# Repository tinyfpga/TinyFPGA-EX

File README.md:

# TinyFPGA-EX
Small, but powerful FPGA development board based on the Lattice ECP5.

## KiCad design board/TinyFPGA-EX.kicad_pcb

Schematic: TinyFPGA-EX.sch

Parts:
C1, C17, C20, C42, C43: 1uF; C_0402_NoSilk
C2, C3, C6, C9, C10, C13, C15, C18, C24, C26, C28, C29, C30, C34, C39, C41, C44, C45, C46, C47: 100nF; C_0402_NoSilk
C4, C7, C11, C12, C14, C16, C31, C35: 10nf; C_0402_NoSilk
C5, C23: 10uF; C_0603
C8, C38, C40: 10nF; C_0402_NoSilk
C19: 2.2uF; C_0402_NoSilk
C22: 22uF; C_0603
C33: 10uF; C_0402_NoSilk
C36, C37: 1nF; C_0402_NoSilk
D1, D2: LED; LED_0603
J1: Conn_02x03_Odd_Even
J2: Micro_SD_Card_Det_Hirose_DM3AT; DM3D-SF
J3: USBC
J4, J5: Conn_01x24; Pin_Header_Straight_1x24_Pitch2.54mm
J6: Conn_02x09_Odd_Even
J7: Conn_01x06
L1: 330nH; L_Vishay_IHLP-1616
L2: 1uH; L_Wuerth_MAPI-2010
R3, R8: 0; R_0402_NoSilk
R4, R5, R7, R10: 4.7k; R_0402_NoSilk
R6: 100K; R_0402_NoSilk
R11: 1.5k; R_0402_NoSilk
R12, R13: 4.7K; R_0402_NoSilk
SW1: SW_Push; PTS_810_SMT_Switch
TP1, TP11, TP12, TP13: TEST; small-testpoint
U1: LFE5UM-285
U2: S27KS0641DPBHI020; FBGA-24
U3: DSC6001CI2A-016.0000T; CDFN3225-4LD-PL-1
U4: FAN53555; WLCSP-20
U5: MIC5504-2.5YMT-TR; Thin-DFN4
U6: Conn_02x03_Counter_Clockwise
U7: FAN53600; WLCSP-6
U8: S25FL064L; UNF008
U9: MIC5504-1.2YMT-TR; Thin-DFN4
U10, U11: PUSB3FR4Z

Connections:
+1V1: C10.1, C12.1, C13.1, C14.1, C15.1, C16.1, C22.1, L1.2, U1.C8, U1.C9, U1.C10, U1.C11, U1.D8, U1.D9, U1.D10, U1.D11, U1.J3, U1.J4, U1.J5, U1.J14, U1.J15, U1.J16, U1.K3, U1.K4, U1.K15, U1.K16, U1.L3, U1.L4, U1.L15, U1.L16, U1.M3, U1.M4, U1.M15, U1.M16, U1.P7, U1.P9, U1.P11, U4.A4; also elsewhere on the board
+1V2A: C36.1, C37.1, C38.1, C39.1, C40.1, C41.1, C43.1, TP1.1, U1.P10, U1.R10, U1.T5, U1.U6, U1.U8, U1.U12, U9.1
+2V5: C6.1, C7.1, C20.1, TP13.1, U1.E6, U1.E13, U1.N6, U1.P5, U1.P13, U1.R3, U5.1
+5V: C5.1, C8.1, C19.1, J3.A4, J3.A9, J3.B4, J3.B9, J5.1, R3.1, U4.A2, U4.D1, U4.D2, U4.E1, U4.E2, U7.A2, U7.B2
CC1: J3.A5
CC2: J3.B5
CFG_MODE_SEL_0: R7.1, U1.U14, U1.V15
CFG_MODE_SEL_1: R5.2, U1.T14
CH0_RXN: J3.A10, U1.V8, U10.2, U10.9
CH0_RXP: J3.A11, U1.V9, U10.1, U10.10
CH0_TXN: C47.2, U1.V11, U11.2, U11.9
CH0_TXP: C45.2, U1.V12, U11.1, U11.10
CH1_RXN: J3.B11, U1.V5, U11.5, U11.6
CH1_RXP: J3.B10, U1.V6, U11.4, U11.7
CH1_TXN: C46.2, U1.V2, U10.5, U10.6
CH1_TXP: C44.2, U1.V3, U10.4, U10.7
CLK_16MHz: U1.B17, U3.3
CSSPIN: U1.U17, U8.1; also elsewhere on the board
DONE: U1.U15
GND: C1.2, C2.2, C3.2, C4.2, C5.2, C6.2, C7.2, C8.2, C9.2, C10.2, C11.2, C12.2, C13.2, C14.2, C15.2, C16.2, C17.2, C18.2, C19.2, C20.2, C22.2, C23.2, C24.2, C26.2, C28.2, C29.2, C30.2, C31.2, C33.2, C34.2, C35.2, C36.2, C37.2, C38.2, C39.2, C40.2, C41.2, C42.2, C43.2, J1.3, J2.6 (VSS), J2.11 (SHIELD), J3.A1, J3.A12, J3.B1, J3.B12, J4.1, J5.2, J5.15, J6.1, R4.2, R6.2, R7.2, R8.2, R12.2, R13.2, SW1.1, U1.B3, U1.B16, U1.E5, U1.E7, U1.E8, U1.E9, U1.E10, U1.E11, U1.E12, U1.E14, U1.F5, U1.F6, U1.F7, U1.F8, U1.F9, U1.F10, U1.F11, U1.F12, U1.F13, U1.F14, U1.G2, U1.G6, U1.G7, U1.G8, U1.G9, U1.G10, U1.G11, U1.G12, U1.G13, U1.G17, U1.H6, U1.H7, U1.H8, U1.H9, U1.H10, U1.H11, U1.H12, U1.H13, U1.J6, U1.J7, U1.J8, U1.J9, U1.J10, U1.J11, U1.J12, U1.J13, U1.K5, U1.K6, U1.K7, U1.K8, U1.K9, U1.K10, U1.K11, U1.K12, U1.K13, U1.K14, U1.L2, U1.L5, U1.L6, U1.L7, U1.L8, U1.L9, U1.L10, U1.L11, U1.L12, U1.L13, U1.L14, U1.L17, U1.M6, U1.M7, U1.M8, U1.M9, U1.M10, U1.M11, U1.M12, U1.M13, U1.N7, U1.N8, U1.N9, U1.N10, U1.N11, U1.N12, U1.P6, U1.P8, U1.P12, U1.R1, U1.R2, U1.T2, U1.T3, U1.T4, U1.T6, U1.T7, U1.T8, U1.T9, U1.T10, U1.T11, U1.T12, U1.T16, U1.U2, U1.U3, U1.U4, U1.U5, U1.U7, U1.U9, U1.U10, U1.U11, U1.V4, U1.V7, U1.V10, U2.B3, U2.C1, U2.E5, U3.2, U4.A3, U4.B1, U4.B2, U4.B3, U4.B4, U4.C1, U4.C2, U4.C3, U4.C4, U5.2, U6.3, U7.A1, U7.C2, U8.4, U9.2, U10.3, U10.8, U11.3, U11.8
INITN: U1.V16
IO2: U1.R18, U8.3
IO3: U1.N18, U8.7
MISO: U1.T18, U8.2; also elsewhere on the board
MOSI: U1.U18, U8.5; also elsewhere on the board
unnamed: C44.1, J3.A3
unnamed: C45.1, J3.B2
unnamed: C46.1, J3.A2
unnamed: C47.1, J3.B3
unnamed: D1.1, R12.1
unnamed: D2.1, R13.1
unnamed: L1.1, U4.D3, U4.D4, U4.E3, U4.E4
unnamed: L2.1, U7.B1
unnamed: R3.2, R8.1, U4.A1
PIN1: J4.2, U1.F18
PIN2: J4.3, U1.H17
PIN3: J4.4, U1.H18
PIN4: J4.5, U1.J17
PIN5: J4.6, U1.N17
PIN6: J4.7, U1.M18
PIN7: J4.8, U1.M17
PIN8: J4.9, U1.G18
PIN9: J4.10, U1.D18
PIN10: J4.11, U1.B18
PIN11: J4.12, U1.A17
PIN12: J4.13, U1.A16
PIN13: J4.14, U1.B15
PIN14: J4.16, U1.A15
PIN15: J4.17, U1.A13
PIN16: J4.18, U1.B13
PIN17: J4.19, U1.D15
PIN18: J4.20, U1.C15
PIN19: J4.21, U1.A11
PIN20: J4.22, U1.B11
PIN21: J4.23, U1.A12
PIN22: J4.24, U1.B12
PIN23: J5.24, U1.B8
PIN24: J5.23, U1.B7
PIN25: J5.22, U1.C4
PIN26: J5.21, U1.B1
PIN27: J5.20, U1.A3
PIN28: J5.19, U1.C2
PIN29: J5.18, U1.C1
PIN30: J5.17, U1.D1
PIN31: J5.16, U1.D3
PIN32: J5.14, U1.R17
PIN33: J5.13, U1.V17
PIN34: J5.12, U1.R16
PIN35: J5.11, U1.J18
PIN36: J5.10, U1.K17
PIN37: J5.9, U1.K18
PIN38: J5.8, U1.L18
PIN39: J5.7, U1.N16
PIN40: J5.6, U1.C17
PIN41: J5.5, U1.C18
PIN42: J5.4, U1.D17
PIN43: J6.21, U1.C3
PIN44: J6.19, U1.F4
PIN45: J6.17, U1.N4
PIN46: J6.15, U1.B6
PIN47: J6.13, U1.A6
PIN48: D2.2, J6.11, U1.A7
PIN49: J6.10, U1.A2
PIN50: J6.12, U1.B2
PIN51: J6.14, U1.B4
PIN52: J6.16, U1.D2
PIN53: J6.18, U1.N3
PIN54: J6.20, U1.N2
PIN55: J6.22, U1.N1
PROGRAMN: R10.2, SW1.2, TP11.1, U1.T15, U1.T17
RAM_CK+: U1.F1, U2.B2
RAM_CS_B: U1.H1, U2.A3
RAM_DQ0: U1.J1, U2.D3
RAM_DQ1: U1.G1, U2.D2
RAM_DQ2: U1.K1, U2.C4
RAM_DQ3: U1.M2, U2.D4
RAM_DQ4: U1.M1, U2.D5
RAM_DQ5: U1.L1, U2.E3
RAM_DQ6: U1.F2, U2.E2
RAM_DQ7: U1.F3, U2.E1
RAM_RESET_B: U1.K2, U2.A4
RAM_RWDS: U1.J2, U2.C3
SBU1: J3.A8, TP12.1
SBU2: J3.B8; also elsewhere on the board
SCK: U1.U16, U8.6; also elsewhere on the board
SDCARD_CLK: J2.5 (CLK), J6.3, U1.B10
SDCARD_CMD: J2.3 (CMD), J6.8, U1.A4
SDCARD_DAT0: J2.7 (DAT0), J6.5, U1.A10
SDCARD_DAT1: J2.8 (DAT1), J6.7, U1.A9
SDCARD_DAT2: J2.1 (DAT2), J6.4, U1.A8
SDCARD_DAT3_CD: J2.2 (DAT3/CD), J6.6, U1.D4
SDCARD_DET: J2.9 (DET_B), J6.9, R6.1, U1.B9
TCK: J1.2, R4.1, U1.U13
TDI: J1.4, U1.T13
TDO: J1.5, U1.V14
TMS: J1.6, U1.V13
USB3_REFCLK_0: U1.U1, U6.4
USB3_REFCLK_1: U1.T1, U6.5
USB_CONNECT: R11.1, U1.C16
USB_D+: J3.A6, J3.B6, R11.2, U1.D16; also elsewhere on the board
USB_D-: J3.A7, J3.B7, U1.F17; also elsewhere on the board
VCCIO0: C1.1, C2.1, C3.1, C4.1, C9.1, C11.1, C17.1, C18.1, C23.1, C24.1, C26.1, C28.1, C29.1, C30.1, C31.1, C33.1, C34.1, C35.1, C42.1, D1.2, J1.1, J2.4 (VDD), J2.10 (DET_A), J4.15, J5.3, J6.2, L2.2, R5.1, R10.1, U1.C6, U1.C7, U1.C12, U1.C13, U1.D6, U1.D7, U1.D12, U1.D13, U1.G4, U1.G5, U1.G14, U1.G15, U1.H4, U1.H5, U1.H14, U1.H15, U1.M5, U1.M14, U1.N5, U1.N13, U1.N14, U1.N15, U1.P14, U2.B4, U2.D1, U2.E4, U3.1, U3.4, U5.3, U5.4, U6.1, U6.6, U7.C1, U8.8, U9.3, U9.4

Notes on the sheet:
Select SPI Master Configuration Mode by setting CFG[2:0] == 3'b010
ECP5 Hardware Checklist recommends using a pull-up on this pin if the FPGA will be using it to handshake with other devices. However, this pin will not be used and should not need an external pull-up.
JTAG Header
Voltage Regulator Tree
1.2 Volt Switching Regulator
3.3 Volt Switching Regulator
2.5 Volt LDO Regulator
JTAG
FPGA Power Supply Connections and Decoupling
FPGA Bitstream Configuration
SPI Configuration Flash
Micro SD Card Slot
HyperRAM
System Clock
USB Type-C Connector
Board Connectors and FPGA IOs
Channel 1 polarity is inverted
1.2 Volt LDO Regulator
USB3 Reference Clock
Place R3 for 1.2v operation Place R8 for 1.1v operation
USB3 FPGA SERDES
Low Speed Signal Breakout
Bottom Header
1.2v LDO is only used for boards with SERDES
Bootloader Button
Power and Status LEDs

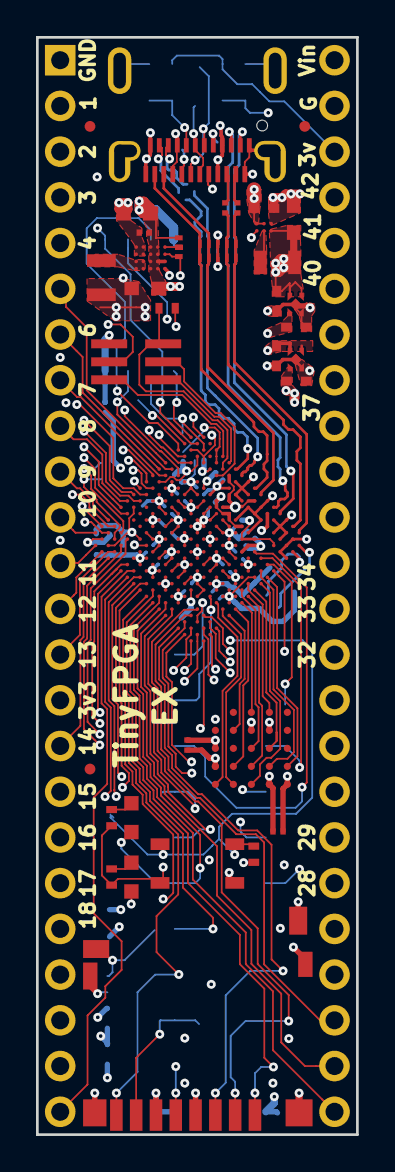
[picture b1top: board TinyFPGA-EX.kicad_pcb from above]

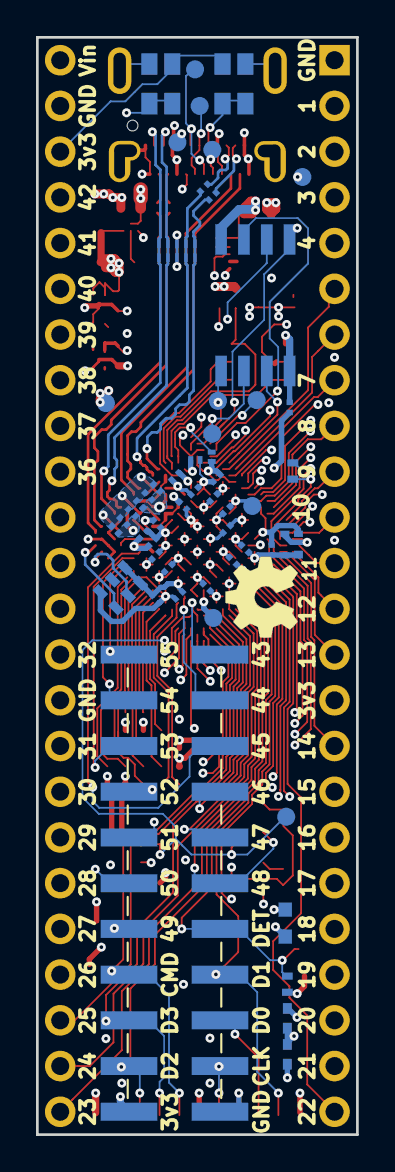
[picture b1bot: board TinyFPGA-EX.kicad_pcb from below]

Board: 6 copper layers, 17.8 x 61.0 mm, 87 parts (51 on the bottom side), 118 nets.

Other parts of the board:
TP12#2, TP12#3, TP12#4, TP12#5, TP12#6, TP12#7, TP12#8, TP12#9: TEST; small-testpoint

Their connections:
+1V1: TP12#9.1; also elsewhere on the board
CSSPIN: TP12#6.1; also elsewhere on the board
MISO: TP12#5.1; also elsewhere on the board
MOSI: TP12#7.1; also elsewhere on the board
SBU2: TP12#2.1; also elsewhere on the board
SCK: TP12#8.1; also elsewhere on the board
USB_D+: TP12#4.1; also elsewhere on the board
USB_D-: TP12#3.1; also elsewhere on the board

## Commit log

2018-11-28 putting TinyFPGA EX on github
2018-11-28 add CERN OHL 1.2
2018-11-28 remove backup and generated files
2019-02-02 latest tweaks
2019-02-04 minor updates for rev c
2019-06-02 wip updates to the EX
